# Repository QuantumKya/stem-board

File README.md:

# stem-board
A custom keypad for typing common characters in science &amp; math that aren't found on the average Latin keyboard.

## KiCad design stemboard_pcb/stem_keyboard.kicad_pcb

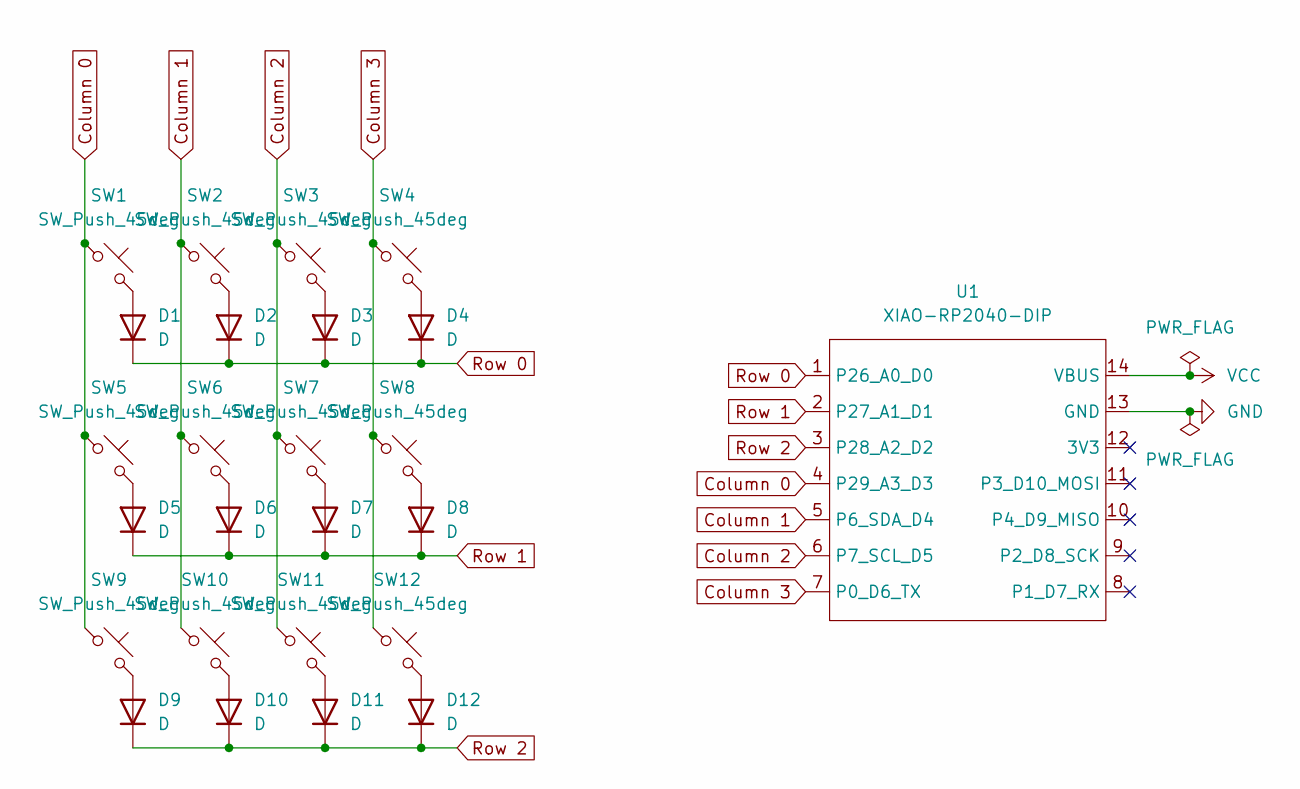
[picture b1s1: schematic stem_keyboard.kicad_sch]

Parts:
D1, D2, D3, D4, D5, D6, D7, D8, D9, D10, D11, D12: D; 1N4148
SW1, SW2, SW3, SW4, SW5, SW6, SW7, SW8, SW9, SW10, SW11, SW12: SW_Push_45deg; SW_Cherry_MX_1.00u_PCB
U1: XIAO-RP2040-DIP

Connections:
Column 0: SW1.1, SW5.1, SW9.1, U1.4 (P29_A3_D3)
Column 1: SW2.1, SW6.1, SW10.1, U1.5 (P6_SDA_D4)
Column 2: SW3.1, SW7.1, SW11.1, U1.6 (P7_SCL_D5)
Column 3: SW4.1, SW8.1, SW12.1, U1.7 (P0_D6_TX)
GND: U1.13 (GND)
unnamed: D1.2 (A), SW1.2
unnamed: D2.2 (A), SW2.2
unnamed: D3.2 (A), SW3.2
unnamed: D4.2 (A), SW4.2
unnamed: D5.2 (A), SW5.2
unnamed: D6.2 (A), SW6.2
unnamed: D7.2 (A), SW7.2
unnamed: D8.2 (A), SW8.2
unnamed: D9.2 (A), SW9.2
unnamed: D10.2 (A), SW10.2
unnamed: D11.2 (A), SW11.2
unnamed: D12.2 (A), SW12.2
Row 0: D1.1 (K), D2.1 (K), D3.1 (K), D4.1 (K), U1.1 (P26_A0_D0)
Row 1: D5.1 (K), D6.1 (K), D7.1 (K), D8.1 (K), U1.2 (P27_A1_D1)
Row 2: D9.1 (K), D10.1 (K), D11.1 (K), D12.1 (K), U1.3 (P28_A2_D2)
VCC: U1.14 (VBUS)

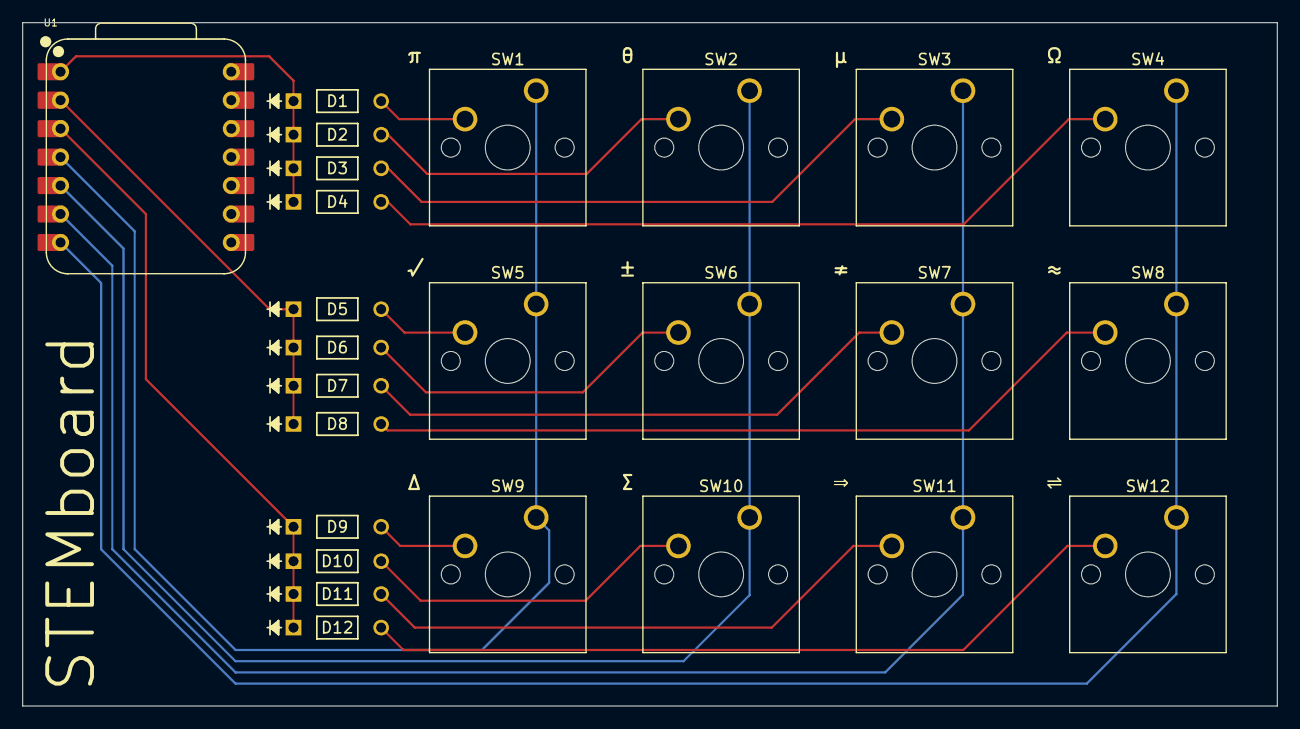
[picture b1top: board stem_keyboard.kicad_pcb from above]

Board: 2 copper layers, 112.0 x 61.0 mm, 25 parts (0 on the bottom side), 19 nets.

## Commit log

2026-06-09 Created KiCad project, finished schematic & PCB
2026-06-10 Finished that PCB & did some Onshape stuff
